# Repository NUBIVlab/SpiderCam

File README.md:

## [CVPR 2026] SpiderCam: Low-Power Snapshot Depth from Differential Defocus

<b>[Marcos A. Ferreira](https://marc103.github.io/)</b><sup>&ast;,1</sup>, <b>[Tianao Li](https://lukeli0425.github.io/)</b><sup>&ast;,1</sup>, <b>[John Mamish](https://scholar.google.com/citations?user=ux9iJ74AAAAJ&hl=en)</b><sup>&ast;,2</sup>, <b>[Josiah Hester](https://josiahhester.com/)</b><sup>2</sup>, <b>[Yaman Sangar](https://scholar.google.com/citations?user=gbBJzRkAAAAJ&hl=en&oi=ao)</b><sup>2</sup>, <b>[Qi Guo](https://www.qiguo.org/)</b><sup>3</sup>, <b>[Emma Alexander](https://www.alexander.vision/emma)</b><sup>1</sup>
<br>
<sup>1</sup>Northwestern University, <sup>2</sup>Georgia Institute of Technology, <sup>3</sup>Purdue University, <sup>&ast;</sup>Equal contribution.

_IEEE/CVF Conference on Computer Vision and Pattern Recognition (CVPR), 2026_

&nbsp;
&nbsp;
&nbsp;
&nbsp;

Official code for [_SpiderCam: Low-Power Snapshot Depth from Differential Defocus_](https://nubivlab.github.io/SpiderCam/).

### Repository layout

| Path | Contents |
| --- | --- |
| [`configs/`](configs/), [`datasets/`](datasets/), [`models/`](models/), [`utils/`](utils/) | Hydra configs and DfDD training / inference code |
| [`serialcam_ft232h/`](serialcam_ft232h/) | Live FT232H stream viewer and on-device DfDD parameter UI |
| [`fpga/`](fpga/) | FPGA RTL (see [`fpga/README.md`](fpga/README.md)) |
| [`pcb/`](pcb/) | PCB layouts |
| [`3d_printed_parts/`](3d_printed_parts/) | Printable enclosure parts |

### Running DfDD

#### Setup

To install required packages:
```bash
pip install -r requirements.txt
```

#### Data

Point `data_path` in a config under [`configs/data/`](configs/data/) to your capture directory. Each group folder should contain paired frames:

- `cam_1_500_480_{idx}.png` — near-focus (`+`) image  
- `cam_0_500_480_{idx}.png` — far-focus (`-`) image  

Crop, frame range, depth step/offset, and image center are set in the same YAML (see e.g. [`configs/data/11-06.yaml`](configs/data/11-06.yaml)).

#### Model parameters

Defaults live in [`configs/model/focal_split.yaml`](configs/model/focal_split.yaml). Override any of them on the CLI with Hydra (`model.<key>=...`).

| Parameter | Options / typical values | Meaning |
| --- | --- | --- |
| `model.n_scales` | `1` or `2` | Number of Laplacian-pyramid levels. Depth is estimated at each scale and fused; `2` is the paper default and improves robustness across texture frequencies. |
| `model.dxdy` | `true` / `false` | If `true`, append spatial derivatives (`∂/∂x`, `∂/∂y`) of `V` and `W` as extra channels before fusion (3 channels per scale). Helps on oriented textures. |
| `model.const` | `rings`, `universal`, `radial`, `polynomial`, `pixel-grid` | How optical constants **A** and **B** vary over the field of view (see below). |
| `model.n_rings` | e.g. `16` | Used when `const=rings`: number of concentric annuli with a shared (A, B) per ring. |
| `model.n_orders` | e.g. `2` | Used when `const=radial` or `polynomial`: polynomial degree of the radial / 2D field. |
| `model.conf` | `VW`, `W2`, `V`, `W` | Confidence map used for sparsity filtering and (in `separate` mode) scale fusion. |
| `model.mode` | `joint` / `separate` | How multi-channel estimates are fused (see below). |

**Optical constants (`model.const`).** DfDD recovers depth from a linear combination of the image Laplacian and the differential image, with learnable maps **A** and **B** (one pair per scale):

- `universal` — single scalar (A, B) per scale (spatially constant; ablation / simplest FPGA mapping).
- `rings` — piecewise-constant (A, B) on concentric rings about `data.center` (paper default; matches on-device zone tables).
- `radial` — A(r), B(r) as low-order polynomials in image radius.
- `polynomial` — full 2D polynomial in (x, y).
- `pixel-grid` — independent (A, B) at every pixel (most flexible, heaviest).

**Confidence (`model.conf`).** With numerator/denominator terms built from `V` and `W`:

- `VW` — confidence ∝ `V·W` (paper default; aligns with the depth numerator).
- `W2` — confidence ∝ `W²` (denominator energy).
- `V` / `W` — confidence ∝ `|V|` or `|W|`.

Higher confidence pixels are kept when evaluating at a given sparsity (see `optim.sparsity`).

**Fusion (`model.mode`).** Softmax weights `ω` combine channels across scales (and dx/dy if enabled):

- `joint` — fuse numerator and denominator first, then divide (more stable; default).
- `separate` — form a depth map per channel, then confidence-weighted average.

**Paper setting (recommended start):**

```text
model.n_scales=2 model.dxdy=true model.mode=joint model.const=rings model.n_rings=16 model.conf=VW
```

#### Train

Calibrate / train optical constants with Hydra overrides:

```bash
python train_focal_split.py data=11-06 data.group=texture1 \
  model.n_scales=2 model.dxdy=true model.mode=joint model.const=rings model.n_rings=16 \
  model.conf=VW
```

Checkpoints and logs are written under `./results/`. For the full ablation suite used in the paper, see [`train.sh`](train.sh).

#### Evaluate

After training, run inference with the same data/model/optim settings (must match the trained checkpoint path):

```bash
python run_focal_split.py data=11-06 data.group=texture1 \
  model.n_scales=2 model.dxdy=true model.mode=joint model.const=rings model.n_rings=16 \
  model.conf=VW
```

This loads `checkpoint_{n_epochs}epochs.pth`, reports MAE/MSE and working range at several sparsities, and saves heatmaps / depth maps under `./results/`.

#### Live hardware (optional)

With the SpiderCam FPGA connected over FT232H:

```bash
python serialcam_ft232h/serialcam_stream_ft232h.py
```

Requires the `serialcam` stack (PyQt5, `ftd2xx`). Use **Set DfDD Parameters** in the viewer to push A/B/ω and confidence thresholds to the device. 
<!-- PCB layouts, FPGA RTL, and printable enclosure parts are under [`pcb/`](pcb/), [`fpga/`](fpga/), and [`3d_printed_parts/`](3d_printed_parts/). -->

### Citation

```bibtex
@InProceedings{ferreira2026spidercam,
    author    = {Ferreira, Marcos A. and Li, Tianao and Mamish, John and Hester, Josiah and Sangar, Yaman and Guo, Qi and Alexander, Emma},
    title     = {SpiderCam: Low-Power Snapshot Depth from Differential Defocus},
    booktitle = {Proceedings of the IEEE/CVF Conference on Computer Vision and Pattern Recognition (CVPR)},
    month     = {June},
    year      = {2026},
    pages     = {41699-41709}
}
```

### Acknowledgment

This research was partially supported by the National Science Foundation under award numbers CNS-2430327 and CCF-2431505. Any opinions, findings, conclusions, or recommendations expressed in this material are those of the authors and do not necessarily reflect the views of the National Science Foundation or other supporters. We would also like to thank [Junjie Luo](https://luo-jun-jie.github.io/) and [Alan Fu](https://www.linkedin.com/in/alan-fu-a100b91a5/) for helpful discussions.

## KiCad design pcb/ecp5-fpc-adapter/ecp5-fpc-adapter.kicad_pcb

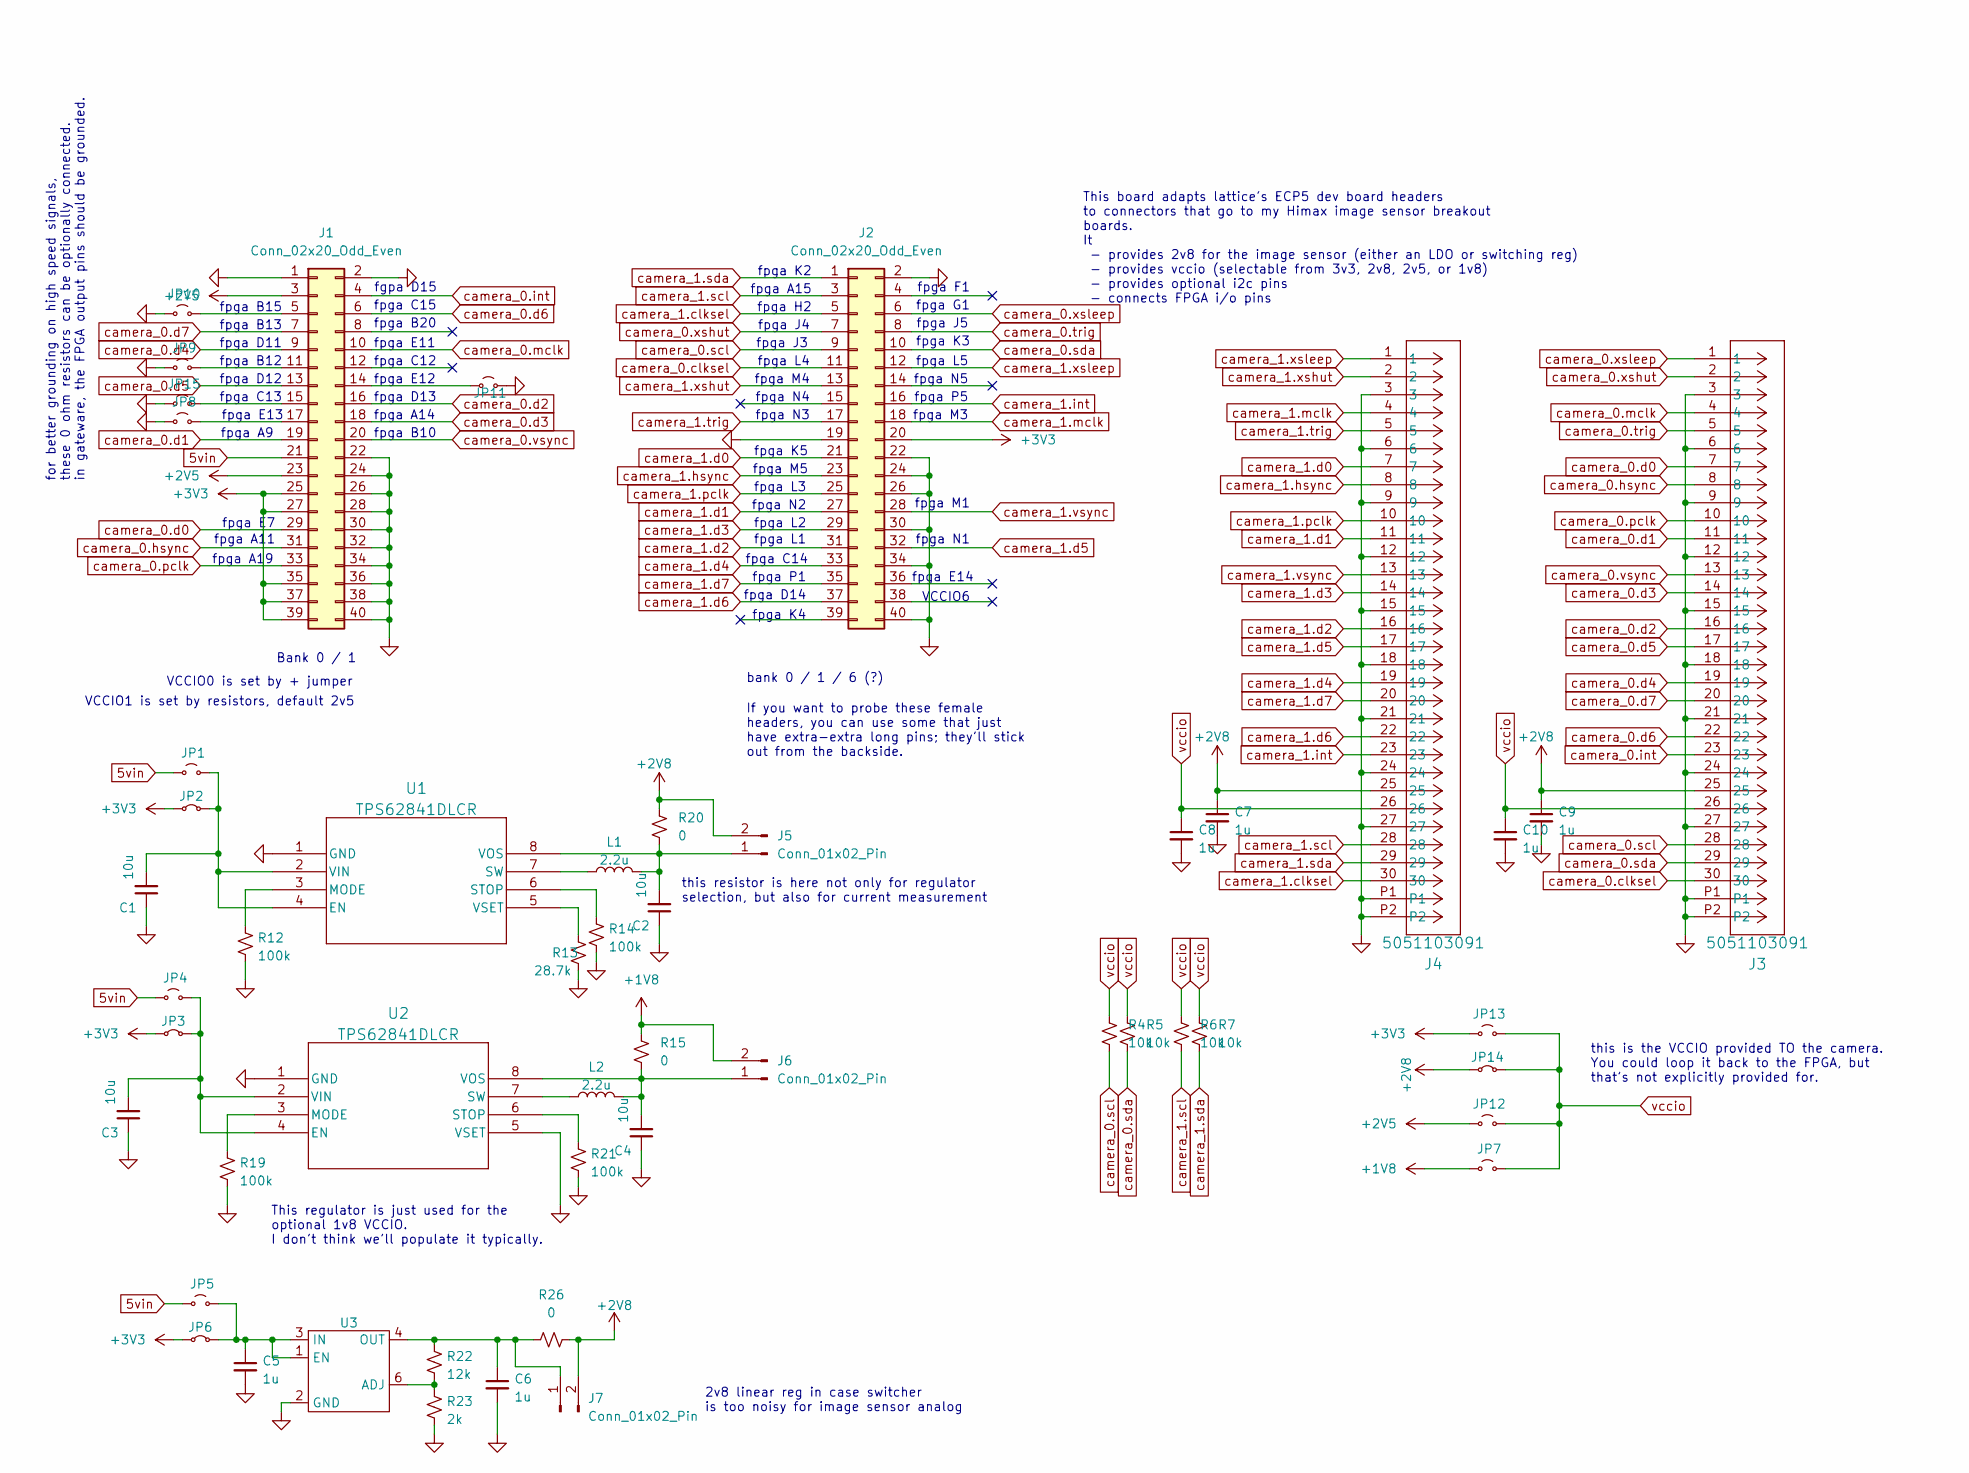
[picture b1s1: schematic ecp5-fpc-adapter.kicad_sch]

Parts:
C1, C2, C3, C4: 10u; C_0603_1608Metric_Pad1.08x0.95mm_HandSolder; MFR_PN CL21A106KOQNNNE
C5, C6, C7, C8, C9, C10: 1u; C_0603_1608Metric_Pad1.08x0.95mm_HandSolder; MFR_PN CL05A105KO5NNNC
J1, J2: Conn_02x20_Odd_Even; PinHeader_2x20_P2.54mm_Vertical
J3, J4: 5051103091; CON_5051103091_MOL
J5, J6, J7: Conn_01x02_Pin; PinHeader_1x02_P2.54mm_Vertical
JP1, JP4, JP5, JP7, JP8, JP9, JP10, JP11, JP12, JP13, JP15: Jumper_2_Small_Open; SolderJumper-2_P1.3mm_Open_RoundedPad1.0x1.5mm
JP2, JP3, JP6, JP14: Jumper_2_Small_Bridged; SolderJumper-2_P1.3mm_Bridged_RoundedPad1.0x1.5mm
L1, L2: 2.2u; IND_DFE2016_MUR; MFR_PN DFE201612E-2R2M=P2
R4, R5, R6, R7: 10k; R_0603_1608Metric_Pad0.98x0.95mm_HandSolder; MFR_PN ERJ-2GE0R00X
R12, R14, R19, R21: 100k; R_0603_1608Metric_Pad0.98x0.95mm_HandSolder; MFR_PN ERJ-2RKF5101X
R13: 28.7k; R_0603_1608Metric_Pad0.98x0.95mm_HandSolder; MFR_PN ERJ-2RKF5101X
R15, R20, R26: 0; R_0603_1608Metric_Pad0.98x0.95mm_HandSolder; MFR_PN ERJ-2GE0R00X
R22: 12k; R_0603_1608Metric_Pad0.98x0.95mm_HandSolder; MFR_PN ERJ-2RKF1202X
R23: 2k; R_0603_1608Metric_Pad0.98x0.95mm_HandSolder; MFR_PN ERJ-2RKF2001X
U1, U2: TPS62841DLCR; VSON8_2P1X1P6_TEX
U3: AP7331-SNG-7; DFN200X200X60-8N; MFR_PN AP7331-SNG-7

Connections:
5vin: J1.21, JP1.1 (A), JP4.1 (A), JP5.1 (A)
+1V8: J6.2, JP7.1 (A), R15.2
+2V5: J1.3, J1.23, JP12.1 (A)
+2V8: C7.1, C9.1, J3.25, J4.25, J5.2, J7.2, JP14.1 (A), R20.2, R26.1
+3V3: J1.25, J1.27, J1.35, J1.37, J1.39, J2.20, JP2.1 (A), JP3.1 (A), JP6.1 (A), JP13.1 (A)
GND: C1.1, C2.1, C3.1, C4.1, C5.2, C6.2, C7.2, C8.2, C9.2, C10.2, J1.1, J1.2, J1.22, J1.24, J1.26, J1.28, J1.30, J1.32, J1.34, J1.36, J1.38, J1.40, J2.2, J2.19, J2.22, J2.24, J2.26, J2.30, J2.34, J2.40, J3.3, J3.6, J3.9, J3.12, J3.15, J3.18, J3.21, J3.24, J3.27, J3.P1, J3.P2, J4.3, J4.6, J4.9, J4.12, J4.15, J4.18, J4.21, J4.24, J4.27, J4.P1, J4.P2, JP8.1 (A), JP9.1 (A), JP10.1 (A), JP11.2 (B), JP15.1 (A), R12.2, R13.2, R14.2, R19.2, R21.2, R23.2, U1.1 (GND), U2.1 (GND), U2.5 (VSET), U3.2 (GND), U3.7 (GNDPAD1), U3.8 (GNDPAD2)
unnamed: J1.5, JP10.2 (B)
unnamed: J1.11, JP9.2 (B)
unnamed: J1.14, JP11.1 (A)
unnamed: J1.15, JP15.2 (B)
unnamed: J1.17, JP8.2 (B)
unnamed: C2.2, J5.1, L1.2, R20.1, U1.8 (VOS)
unnamed: C4.2, J6.1, L2.2, R15.1, U2.8 (VOS)
unnamed: C6.1, J7.1, R22.1, R26.2, U3.4 (OUT)
unnamed: C1.2, JP1.2 (B), JP2.2 (B), U1.2 (VIN), U1.4 (EN)
unnamed: C3.2, JP3.2 (B), JP4.2 (B), U2.2 (VIN), U2.4 (EN)
unnamed: C5.1, JP5.2 (B), JP6.2 (B), U3.1 (EN), U3.3 (IN)
unnamed: R12.1, U1.3 (MODE)
unnamed: R14.1, U1.6 (STOP)
unnamed: L1.1, U1.7 (SW)
unnamed: R13.1, U1.5 (VSET)
unnamed: R19.1, U2.3 (MODE)
unnamed: R21.1, U2.6 (STOP)
unnamed: L2.1, U2.7 (SW)
unnamed: R22.2, R23.1, U3.6 (ADJ)
camera_0.clksel: J2.11, J3.30
camera_0.d0: J1.29, J3.7
camera_0.d1: J1.19, J3.11
camera_0.d2: J1.16, J3.16
camera_0.d3: J1.18, J3.14
camera_0.d4: J1.9, J3.19
camera_0.d5: J1.13, J3.17
camera_0.d6: J1.6, J3.22
camera_0.d7: J1.7, J3.20
camera_0.hsync: J1.31, J3.8
camera_0.int: J1.4, J3.23
camera_0.mclk: J1.10, J3.4
camera_0.pclk: J1.33, J3.10
camera_0.scl: J2.9, J3.28, R4.1
camera_0.sda: J2.10, J3.29, R5.1
camera_0.trig: J2.8, J3.5
camera_0.vsync: J1.20, J3.13
camera_0.xshut: J2.7, J3.2
camera_0.xsleep: J2.6, J3.1
camera_1.clksel: J2.5, J4.30
camera_1.d0: J2.21, J4.7
camera_1.d1: J2.27, J4.11
camera_1.d2: J2.31, J4.16
camera_1.d3: J2.29, J4.14
camera_1.d4: J2.33, J4.19
camera_1.d5: J2.32, J4.17
camera_1.d6: J2.37, J4.22
camera_1.d7: J2.35, J4.20
camera_1.hsync: J2.23, J4.8
camera_1.int: J2.16, J4.23
camera_1.mclk: J2.18, J4.4
camera_1.pclk: J2.25, J4.10
camera_1.scl: J2.3, J4.28, R6.1
camera_1.sda: J2.1, J4.29, R7.1
camera_1.trig: J2.17, J4.5
camera_1.vsync: J2.28, J4.13
camera_1.xshut: J2.13, J4.2
camera_1.xsleep: J2.12, J4.1
vccio: C8.1, C10.1, J3.26, J4.26, JP7.2 (B), JP12.2 (B), JP13.2 (B), JP14.2 (B), R4.2, R5.2, R6.2, R7.2

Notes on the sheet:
fpga E14
fpga E13
fpga N1
fpga D13
fpga E12
this is the VCCIO provided TO the camera. You could loop it back to the FPGA, but that's not explicitly provided for.
fpga K5
fpga B20
fpga J4
fpga B10
fpga L5
fpga L3
fpga B13
fpga M3
fpga A9
fpga L1
fpga M1
fpga A15
fpga H2
fpga N4
fpga C13
fpga K2
fpga J3
fpga N3
fpga F1
fpga C12
bank 0 / 1 / 6 (?)
this resistor is here not only for regulator selection, but also for current measurement
This board adapts lattice's ECP5 dev board headers to connectors that go to my Himax image sensor breakout boards. It - provides 2v8 for the image sensor (either an LDO or switching reg) - provides vccio (selectable from 3v3, 2v8, 2v5, or 1v8) - provides optional i2c pins - connects FPGA i/o pins
fpga E7
fpga B12
fpga J5
fpga D12
fpga P5
If you want to probe these female headers, you can use some that just have extra-extra long pins; they'll stick out from the backside.
fpga A19
fpga K3
fpga B15
fpga N5
fpga M4

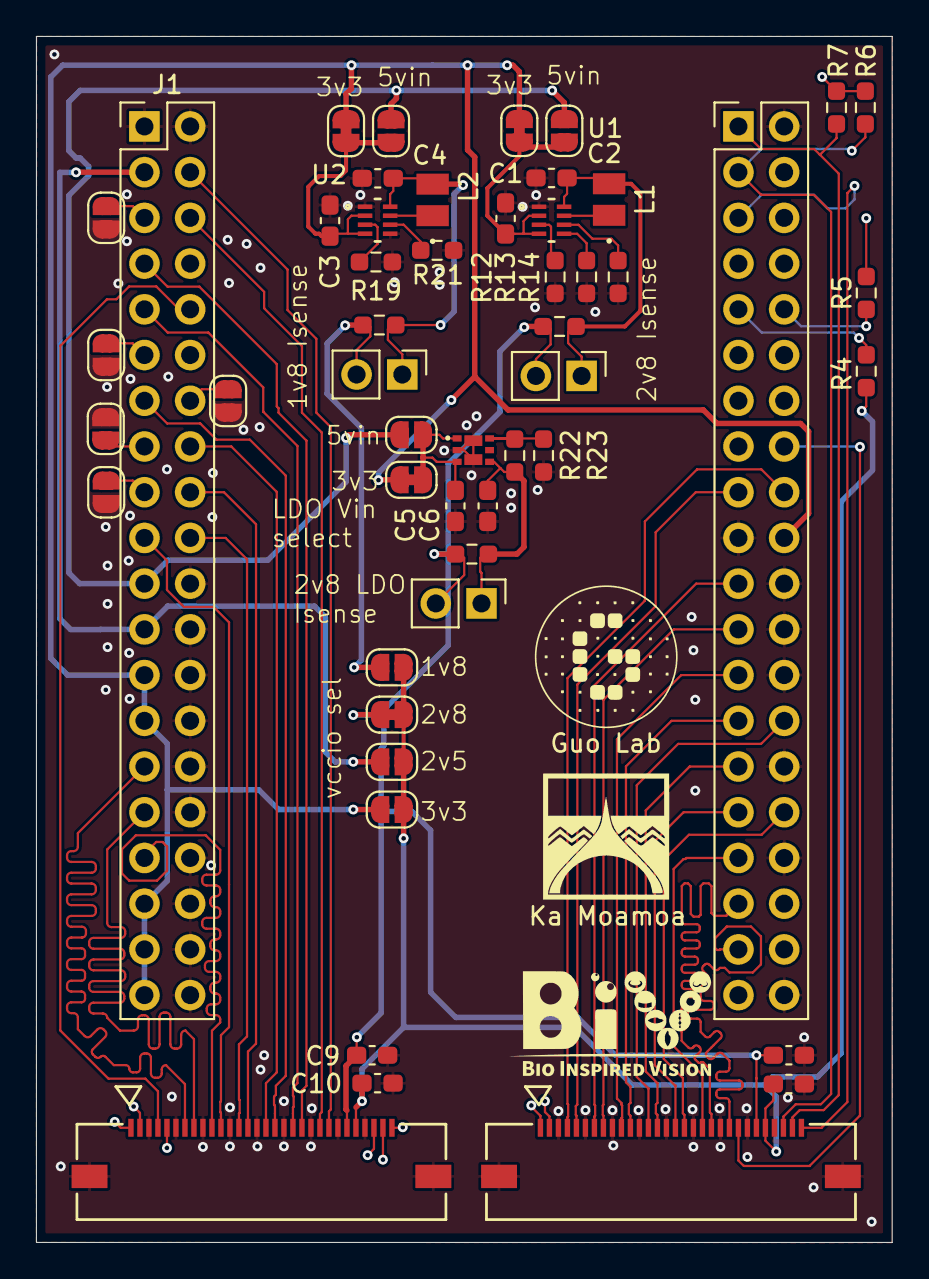
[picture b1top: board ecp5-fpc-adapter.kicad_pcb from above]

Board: 4 copper layers, 47.5 x 67.0 mm, 51 parts (0 on the bottom side), 64 nets.

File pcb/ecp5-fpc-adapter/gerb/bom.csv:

"Reference","Value","Datasheet","Footprint","Qty","DNP"
"C1,C2,C3,C4","10u","~","Capacitor_SMD:C_0603_1608Metric_Pad1.08x0.95mm_HandSolder","4",""
"C5,C6,C7,C8,C9,C10","1u","~","Capacitor_SMD:C_0603_1608Metric_Pad1.08x0.95mm_HandSolder","6",""
"J1,J2","Conn_02x20_Odd_Even","~","Connector_PinHeader_2.54mm:PinHeader_2x20_P2.54mm_Vertical","2",""
"J3,J4","5051103091","5051103091","molex_5051:CON_5051103091_MOL","2",""
"J5,J6,J7","Conn_01x02_Pin","~","Connector_PinHeader_2.54mm:PinHeader_1x02_P2.54mm_Vertical","3",""
"JP1,JP4,JP5,JP7,JP8,JP9,JP10,JP11,JP12,JP13,JP15","Jumper_2_Small_Open","~","Jumper:SolderJumper-2_P1.3mm_Open_RoundedPad1.0x1.5mm","11",""
"JP2,JP3,JP6,JP14","Jumper_2_Small_Bridged","~","Jumper:SolderJumper-2_P1.3mm_Bridged_RoundedPad1.0x1.5mm","4",""
"L1,L2","2.2u","~","L_2016:IND_DFE2016_MUR","2",""
"R4,R5,R6,R7","10k","~","Resistor_SMD:R_0603_1608Metric_Pad0.98x0.95mm_HandSolder","4",""
"R12,R14,R19,R21","100k","~","Resistor_SMD:R_0603_1608Metric_Pad0.98x0.95mm_HandSolder","4",""
"R13","28.7k","~","Resistor_SMD:R_0603_1608Metric_Pad0.98x0.95mm_HandSolder","1",""
"R15,R20,R26","0","~","Resistor_SMD:R_0603_1608Metric_Pad0.98x0.95mm_HandSolder","3",""
"R22","12k","~","Resistor_SMD:R_0603_1608Metric_Pad0.98x0.95mm_HandSolder","1",""
"R23","2k","~","Resistor_SMD:R_0603_1608Metric_Pad0.98x0.95mm_HandSolder","1",""
"U1,U2","TPS62841DLCR","TPS62840DLCR","tps62840:VSON8_2P1X1P6_TEX","2",""
"U3","AP7331-SNG-7","","AP7331-SNG-7:DFN200X200X60-8N","1",""

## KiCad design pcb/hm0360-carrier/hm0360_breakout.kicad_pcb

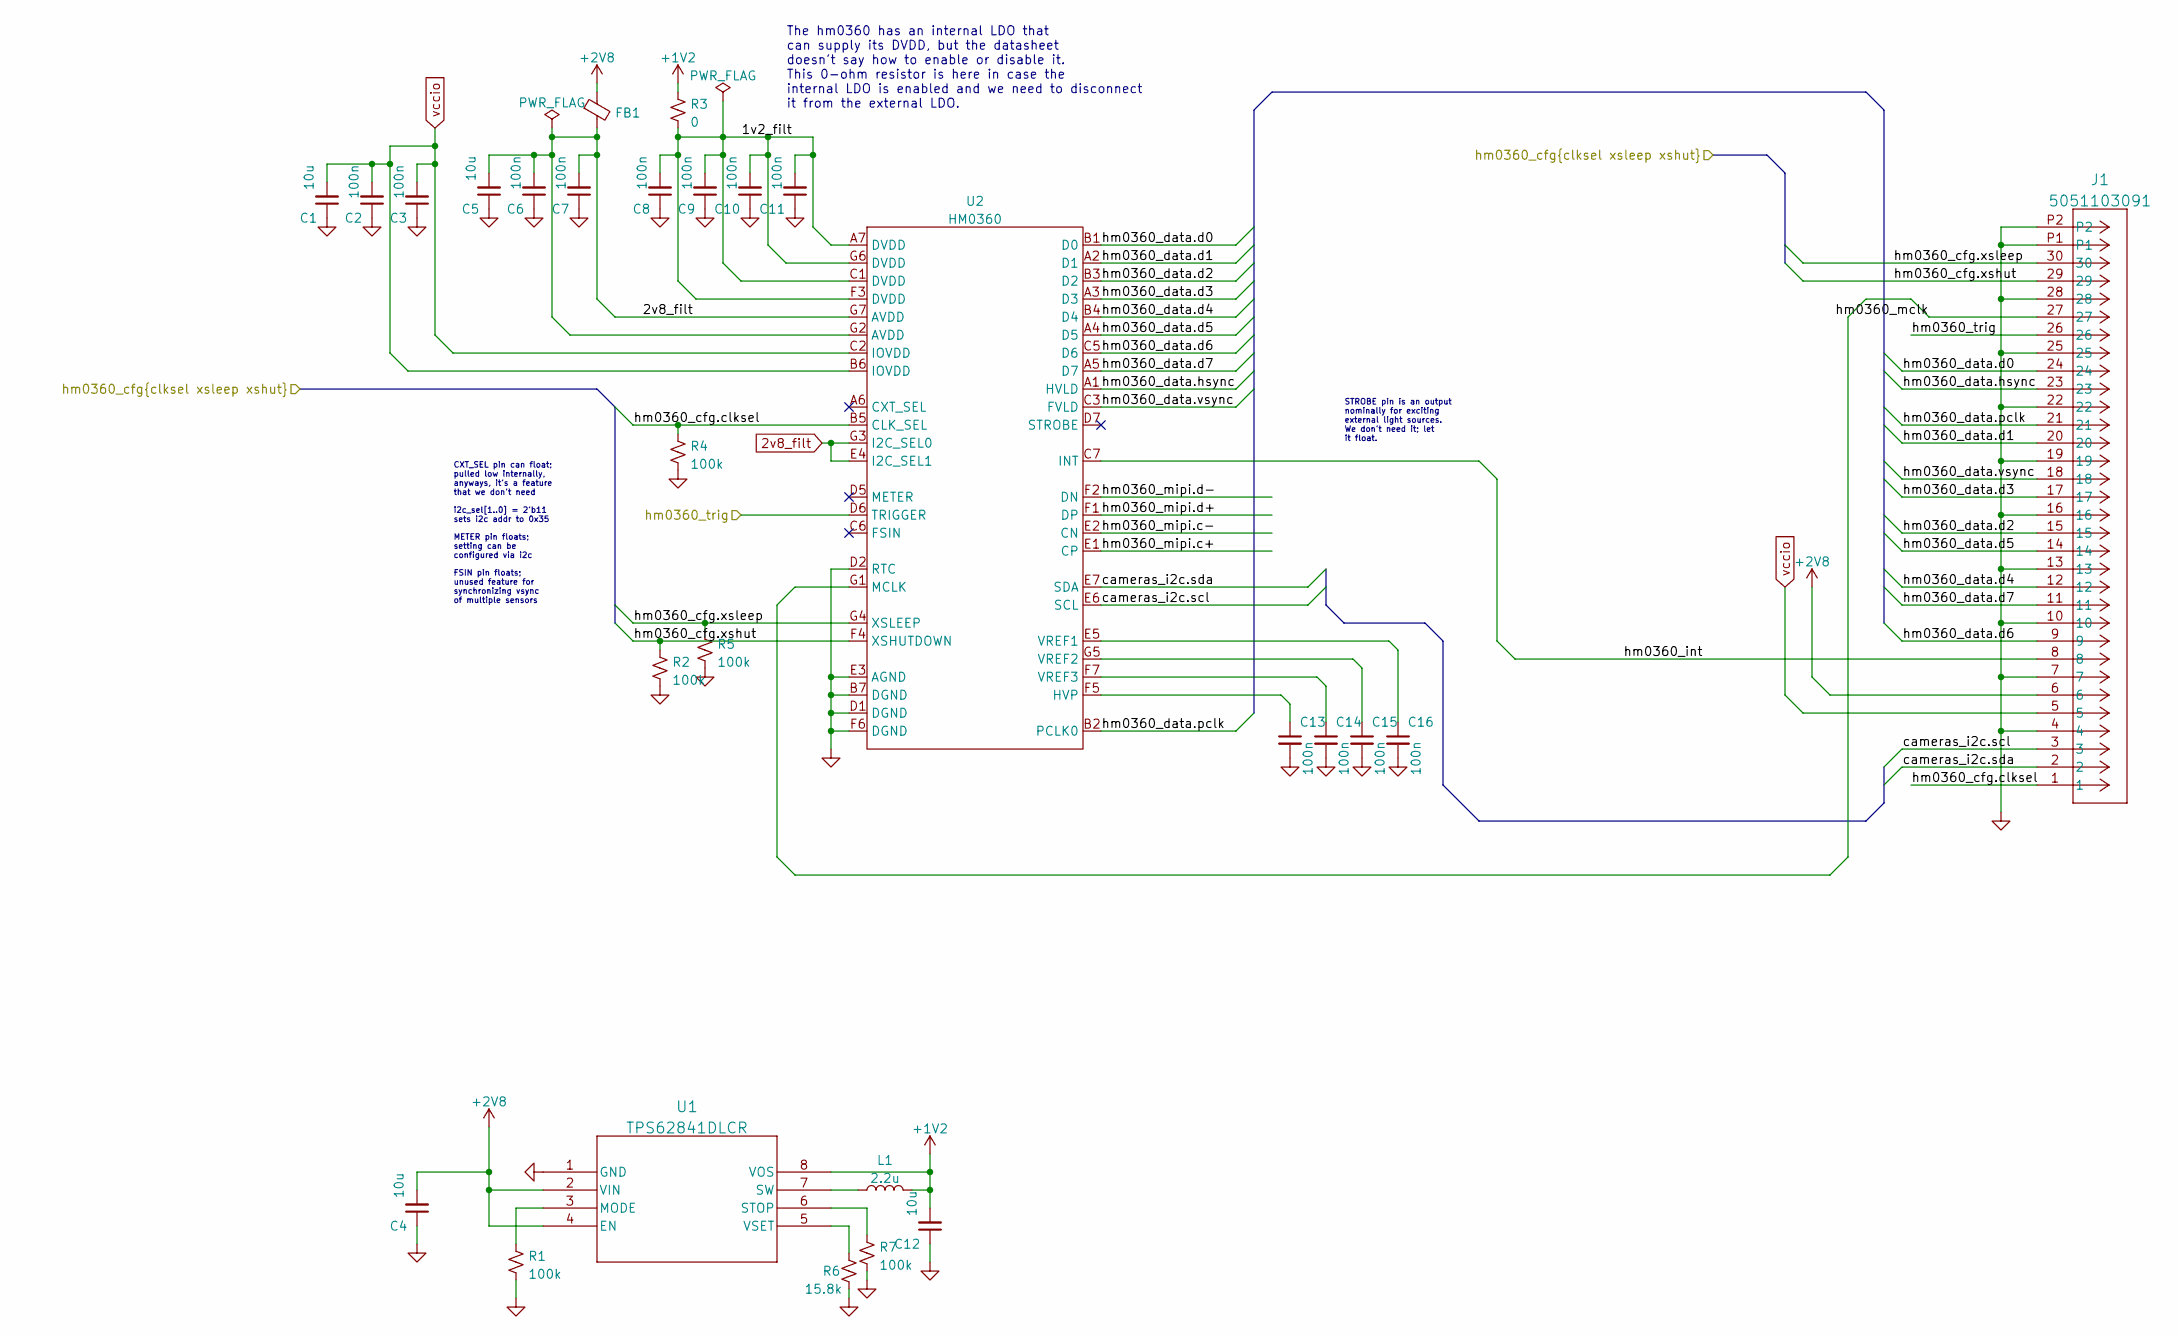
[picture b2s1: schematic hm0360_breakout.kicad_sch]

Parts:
C1, C4, C5, C12: 10u; C_0603_1608Metric; MFR_PN CL21A106KOQNNNE
C2, C3, C6, C7, C8, C9, C10, C11, C13, C14, C15, C16: 100n; C_0201_0603Metric; MFR_PN CL05B104KP5NNNC
FB1: FerriteBead_Small; C_0603_1608Metric; MFR_PN MPZ1608B471ATA00
J1: 5051103091; CON_5051103091_MOL
L1: 2.2u; IND_DFE2016_MUR; MFR_PN DFE201612E-2R2M=P2
R1, R2, R4, R5, R7: 100k; R_0201_0603Metric; MFR_PN ERJ-2RKF5101X
R3: 0; R_0201_0603Metric; MFR_PN ERJ-2GE0R00X
R6: 15.8k; R_0402_1005Metric; MFR_PN ERJ-2RKF5101X
U1: TPS62841DLCR; VSON8_2P1X1P6_TEX
U2: HM0360; hm0360; MFR_PN HM0360-MWA

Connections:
2v8_filt: C5.2, C6.2, C7.2, FB1.2, U2.E4 (I2C_SEL1), U2.G2 (AVDD), U2.G3 (I2C_SEL0), U2.G7 (AVDD)
+1V2: C12.2, L1.2, R3.1, U1.8 (VOS)
+2V8: C4.2, FB1.1, J1.6, U1.2 (VIN), U1.4 (EN)
/1v2_filt: C8.2, C9.2, C10.2, C11.2, R3.2, U2.A7 (DVDD), U2.C1 (DVDD), U2.F3 (DVDD), U2.G6 (DVDD)
/cameras_i2c.scl: J1.3, U2.E6 (SCL)
/cameras_i2c.sda: J1.2, U2.E7 (SDA)
/hm0360_cfg.clksel: J1.1, R4.1, U2.B5 (CLK_SEL)
/hm0360_cfg.xshut: J1.29, R2.1, U2.F4 (XSHUTDOWN)
/hm0360_cfg.xsleep: J1.30, R5.1, U2.G4 (XSLEEP)
/hm0360_data.d0: J1.24, U2.B1 (D0)
/hm0360_data.d1: J1.20, U2.A2 (D1)
/hm0360_data.d2: J1.15, U2.B3 (D2)
/hm0360_data.d3: J1.17, U2.A3 (D3)
/hm0360_data.d4: J1.12, U2.B4 (D4)
/hm0360_data.d5: J1.14, U2.A4 (D5)
/hm0360_data.d6: J1.9, U2.C5 (D6)
/hm0360_data.d7: J1.11, U2.A5 (D7)
/hm0360_data.hsync: J1.23, U2.A1 (HVLD)
/hm0360_data.pclk: J1.21, U2.B2 (PCLK0)
/hm0360_data.vsync: J1.18, U2.C3 (FVLD)
/hm0360_int: J1.8, U2.C7 (INT)
/hm0360_mclk: J1.27, U2.G1 (MCLK)
/hm0360_mipi.c+: U2.E1 (CP)
/hm0360_mipi.c-: U2.E2 (CN)
/hm0360_mipi.d+: U2.F1 (DP)
/hm0360_mipi.d-: U2.F2 (DN)
/hm0360_trig: J1.26, U2.D6 (TRIGGER)
GND: C1.1, C2.1, C3.1, C4.1, C5.1, C6.1, C7.1, C8.1, C9.1, C10.1, C11.1, C12.1, C13.2, C14.2, C15.2, C16.2, J1.4, J1.7, J1.10, J1.13, J1.16, J1.19, J1.22, J1.25, J1.28, J1.P1, J1.P2, R1.2, R2.2, R4.2, R5.2, R6.2, R7.2, U1.1 (GND), U2.B7 (DGND), U2.D1 (DGND), U2.D2 (RTC), U2.E3 (AGND), U2.F6 (DGND)
unnamed: C13.1, U2.F5 (HVP)
unnamed: C14.1, U2.F7 (VREF3)
unnamed: C15.1, U2.G5 (VREF2)
unnamed: C16.1, U2.E5 (VREF1)
unnamed: L1.1, U1.7 (SW)
unnamed: R1.1, U1.3 (MODE)
unnamed: R6.1, U1.5 (VSET)
unnamed: R7.1, U1.6 (STOP)
vccio: C1.2, C2.2, C3.2, J1.5, U2.B6 (IOVDD), U2.C2 (IOVDD)

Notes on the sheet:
FSIN pin floats; unused feature for synchronizing vsync of multiple sensors
CXT_SEL pin can float; pulled low internally, anyways, it's a feature that we don't need
STROBE pin is an output nominally for exciting external light sources. We don't need it; let it float.
i2c_sel[1..0] = 2'b11 sets i2c addr to 0x35
The hm0360 has an internal LDO that can supply its DVDD, but the datasheet doesn't say how to enable or disable it. This 0-ohm resistor is here in case the internal LDO is enabled and we need to disconnect it from the external LDO.
METER pin floats; setting can be configured via i2c

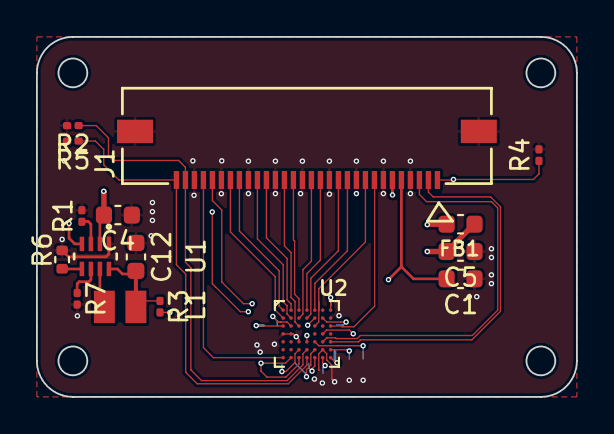
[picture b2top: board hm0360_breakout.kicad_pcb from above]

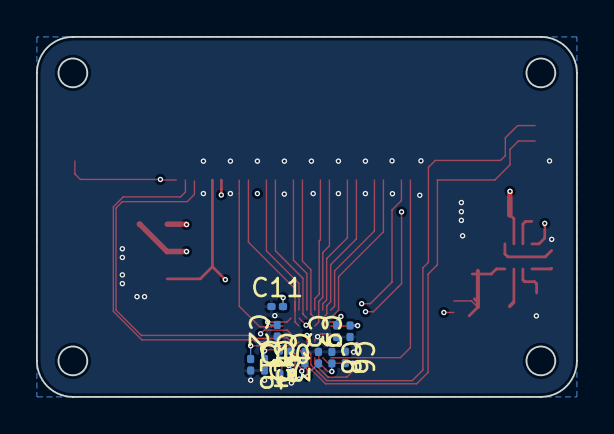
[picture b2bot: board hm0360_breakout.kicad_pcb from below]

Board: 4 copper layers, 30.0 x 20.0 mm, 28 parts (12 on the bottom side), 33 nets.

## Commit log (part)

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2026-03-09 Update README with project title and placeholder
    Added a placeholder for upcoming content.
2026-03-13 uploaded fpga code, pcb adapter parts and 3d printed parts models
2026-03-13 adjusted filenames
2026-03-13 adding .bit files
2026-03-13 added camera previewer bit file
2026-03-13 Update project title and add calibration section
2026-03-13 edited readme

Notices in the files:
README.md:
License: MIT
